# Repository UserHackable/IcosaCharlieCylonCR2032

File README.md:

## IcosaCharlieCylon 

### Board dimensions

* (259951, 99961) original units
* (2.5995, 0.9996) inches
* (66.0276, 25.3901) mm

| Front | Back |
| --- | --- |
|  |  |

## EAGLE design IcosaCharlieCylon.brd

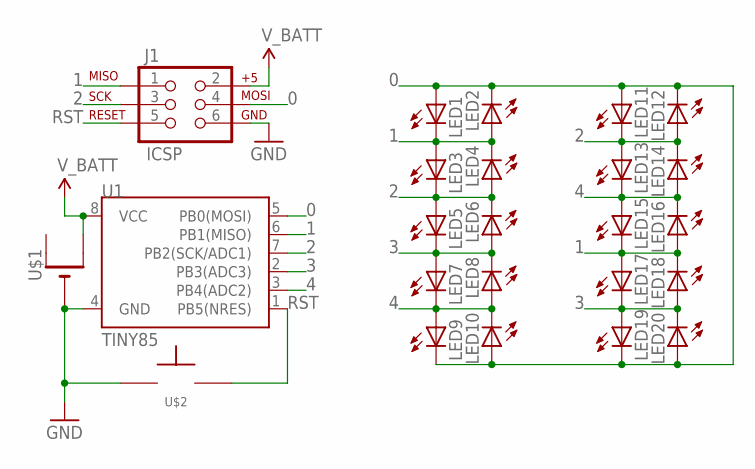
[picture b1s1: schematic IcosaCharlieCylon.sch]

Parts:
J1: ICSP; 2X3-NS
LED1, LED2, LED3, LED4, LED5, LED6, LED7, LED8, LED9, LED10, LED11, LED12, LED13, LED14, LED15, LED16, LED17, LED18, LED19, LED20: LEDOVAL; LED-OVAL
U1: TINY85; DIP08
U$1: CR2032THM; CR2032-THRU
U$2: TAC_SPST_NO

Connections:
0: J1.4 (MOSI), LED1.ANODE (A), LED2.CATHODE (C), LED9.CATHODE (C), LED10.ANODE (A), LED11.ANODE (A), LED12.CATHODE (C), LED19.CATHODE (C), LED20.ANODE (A), U1.5 (PB0(MOSI))
1: J1.1 (MISO), LED1.CATHODE (C), LED2.ANODE (A), LED3.ANODE (A), LED4.CATHODE (C), LED15.CATHODE (C), LED16.ANODE (A), LED17.ANODE (A), LED18.CATHODE (C), U1.6 (PB1(MISO))
2: J1.3 (SCK), LED3.CATHODE (C), LED4.ANODE (A), LED5.ANODE (A), LED6.CATHODE (C), LED11.CATHODE (C), LED12.ANODE (A), LED13.ANODE (A), LED14.CATHODE (C), U1.7 (PB2(SCK/ADC1))
3: LED5.CATHODE (C), LED6.ANODE (A), LED7.ANODE (A), LED8.CATHODE (C), LED17.CATHODE (C), LED18.ANODE (A), LED19.ANODE (A), LED20.CATHODE (C), U1.2 (PB3(ADC3))
4: LED7.CATHODE (C), LED8.ANODE (A), LED9.ANODE (A), LED10.CATHODE (C), LED13.CATHODE (C), LED14.ANODE (A), LED15.ANODE (A), LED16.CATHODE (C), U1.3 (PB4(ADC2))
GND: J1.6 (GND), U1.4 (GND), U$1.-, U$2.P$1
RST: J1.5 (RST), U1.1 (PB5(NRES)), U$2.P$2
V_BATT: J1.2 (V+), U1.8 (VCC), U$1.+2 (+1)

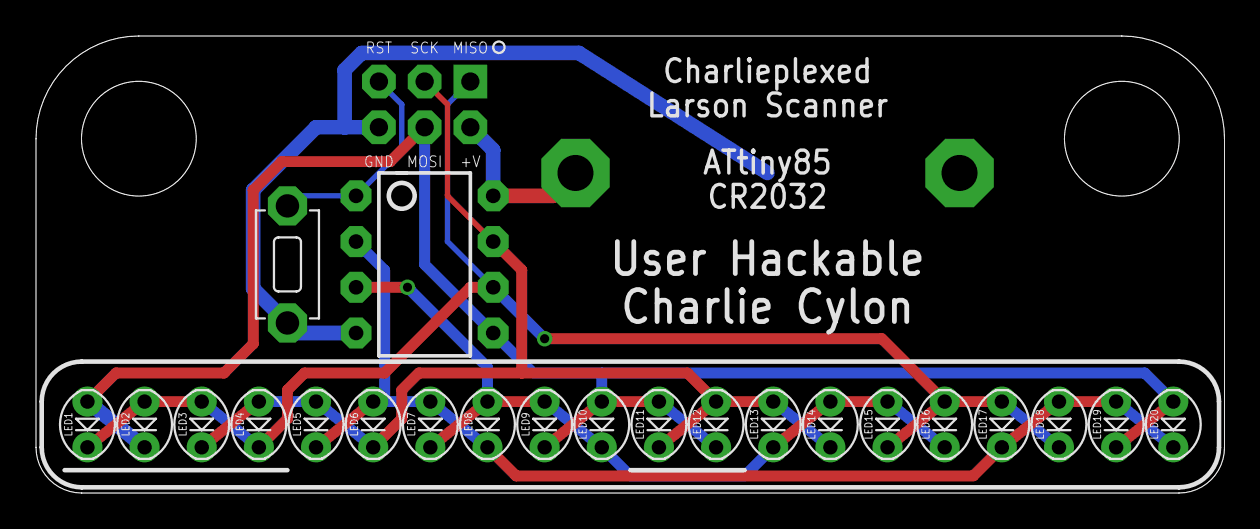
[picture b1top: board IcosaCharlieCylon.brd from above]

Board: 2 copper layers, 66.0 x 25.4 mm, 24 parts (1 on the bottom side), 8 nets.

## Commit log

2016-04-07 from Makefile

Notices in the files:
parts and their libraries:
SparkFun-DigitalIC: Licensing: Creative Commons ShareAlike 4.0 International - https://creativecommons.org/licenses/by-sa/4.0
